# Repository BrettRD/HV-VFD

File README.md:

# HV-VFD
Staging point for design of a motor controller to suit electric vehicles.

This project is intended as a rework of https://github.com/vedderb/bldc-hardware/ to suit systems operating beyond the power ratings of the VESC 4.x.

## Major design goals:
* 400V tolerant system.
* 400A overcurrent survivability.
* FET desaturation detection.
* Maximise forward compatibility with existing development efforts.
* Traction power and logic level isolation
* Flexibility for alternate applications.

### FETs
This design will be based on the SEMiX402GB066HDs by Semikron, but will hopefully support everything in their SEMiX_2s pack.  
This sets the price point fairly high, but will require a rock solid gate driver design.  
I expect this project to branch for different IGBT sizes.  

### FET Drivers
The FET drivers need an estimated 6A to reach 400A IGBTs  
Currently designing around the 1EDI60H12AH by infineon

### Desaturation detector / phase shunt monitor
Depending on the required bandwidth for the phase shunts, a PWM based isolation amp like the IRF2277 might suffice.  
This design will also include a Vsat monitor on all fets, but probably just a fast comparator.  
Current best practice for IGBTs seems to be soft shutdown at some Vsat threshold, for MOSFETs Vsat only helps with estimating the total instantaneous heat power per junction.  

### Architecture
External logic lines will not be linked to traction power in any way.  
High voltage gate drivers are isolated by default, and are mostly available as single-gate drivers.  
Gate handling logic will be on the logic-side, so desat detect and shunt monitoring will all require isolation.  
Given the FET package and the current, the shunts will almost certainly be off-board which makes Hall effect sensors less of a design change.

## Considerations:
### Phase or Rail shunts:  
Phase shunt amplifiers need seperate power supplies and isolation gear, offset calibration is less trivial.  
Phase shunts measure both incoming and outgoing current. KCL should apply to the motor but when it doesn't, you want to know. This also allows automatic gain calibration.  
VESC5 looks like using phase shunts. Using isolation amps, this design could be left configurable. or I could include both.

### Crazy shit not yet dismissed:
* FPGA gate handling logic (iCE40 with yosys)  
  This allows us to do interesting things to the gate drive signals like configurable dead-time/overlap, spike quenching, fast ADCs and thermal modelling of FET junctions.
  Upgrading to the STM32F405VG (100pin pack) offers a 16b wide 80MHz DMA bus.
* ADCs on traction side of isolation barrier.  
  Saves on isolation amplifiers and noise.  
  The STM32F4 has a really nice ADC architecture with custom triggers, DMA, and 12b 6MS/s over 24 channels.

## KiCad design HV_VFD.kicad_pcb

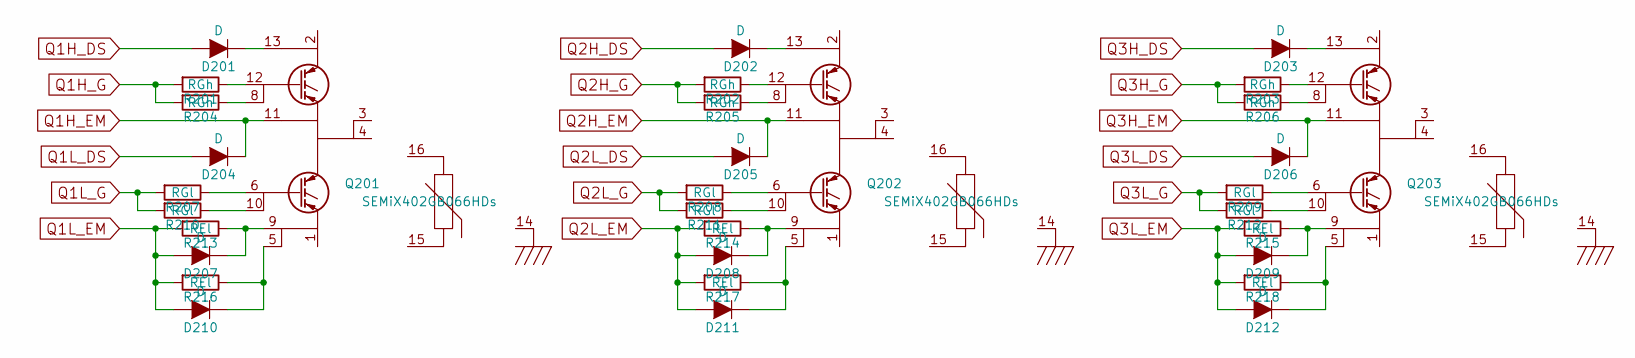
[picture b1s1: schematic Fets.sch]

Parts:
D201, D202, D203, D204, D205, D206: D; MELF_Standard
D207, D208, D209, D210, D211, D212: D; DO-214AB
Q201, Q202, Q203: SEMiX402GB066HDs; SEMiX_2s_7nc
R201, R202, R203, R204, R205, R206: RGh; R_1812
R207, R208, R209, R210, R211, R212: RGl; R_1812
R213, R214, R215, R216, R217, R218: REl; R_1812

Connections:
unnamed: D201.1 (K), Q201.13
unnamed: D202.1 (K), Q202.13
unnamed: D203.1 (K), Q203.13
unnamed: D207.1 (K), Q201.9, R213.1
unnamed: D208.1 (K), Q202.9, R214.1
unnamed: D209.1 (K), Q203.9, R215.1
unnamed: D210.1 (K), Q201.5, R216.1
unnamed: D211.1 (K), Q202.5, R217.1
unnamed: D212.1 (K), Q203.5, R218.1
unnamed: Q201.6, R207.1
unnamed: Q201.8, R204.1
unnamed: Q201.10, R210.1
unnamed: Q201.12, R201.1
unnamed: Q202.6, R208.1
unnamed: Q202.8, R205.1
unnamed: Q202.10, R211.1
unnamed: Q202.12, R202.1
unnamed: Q203.6, R209.1
unnamed: Q203.8, R206.1
unnamed: Q203.10, R212.1
unnamed: Q203.12, R203.1
Q1H_DS: D201.2 (A); also elsewhere on the board
Q1H_EM: D204.1 (K), Q201.11; also elsewhere on the board
Q1H_G: R201.2, R204.2; also elsewhere on the board
Q1L_DS: D204.2 (A); also elsewhere on the board
Q1L_G: R207.2, R210.2; also elsewhere on the board
Q2H_DS: D202.2 (A); also elsewhere on the board
Q2H_EM: D205.1 (K), Q202.11; also elsewhere on the board
Q2H_G: R202.2, R205.2; also elsewhere on the board
Q2L_DS: D205.2 (A); also elsewhere on the board
Q2L_G: R208.2, R211.2; also elsewhere on the board
Q3H_DS: D203.2 (A); also elsewhere on the board
Q3H_EM: D206.1 (K), Q203.11; also elsewhere on the board
Q3H_G: R203.2, R206.2; also elsewhere on the board
Q3L_DS: D206.2 (A); also elsewhere on the board
Q3L_G: R209.2, R212.2; also elsewhere on the board

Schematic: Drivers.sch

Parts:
C301, C302, C303, C304, C305, C306: C; C_1206
D301, D302, D303: D; MELF_Standard
R301, R302, R303, R310, R311, R312: R; R_0603
R304, R305, R306, R307, R308, R309: R; R_1812
U301, U302, U303, U304, U305, U306: 1EDI60H12AH; PG-DSO-8-59

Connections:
+15V: C301.1, C303.1, C305.1, D301.2 (A), D302.2 (A), D303.2 (A), R310.2, R311.2, R312.2, U304.6, U305.6, U306.6
GNDD: U301.3, U301.4, U302.4, U303.4, U304.4, U305.4, U306.4
unnamed: R304.2, U301.7
unnamed: R305.2, U302.7
unnamed: R306.2, U303.7
unnamed: R307.2, U304.7
unnamed: R308.2, U305.7
unnamed: R309.2, U306.7
unnamed: U301.2, U304.3
Q1H_BS: C302.1, D301.1 (K), R301.2, U301.6
Q1H_DS: R301.1; also elsewhere on the board
Q1H_EM: C302.2, U301.5; also elsewhere on the board
Q1H_G: R304.1, U301.8; also elsewhere on the board
Q1L_DS: R310.1; also elsewhere on the board
Q1L_G: R307.1, U304.8; also elsewhere on the board
Q2H_BS: C304.1, D302.1 (K), R302.2, U302.6
Q2H_DS: R302.1; also elsewhere on the board
Q2H_EM: C304.2, U302.5; also elsewhere on the board
Q2H_G: R305.1, U302.8; also elsewhere on the board
Q2L_DS: R311.1; also elsewhere on the board
Q2L_G: R308.1, U305.8; also elsewhere on the board
Q3H_BS: C306.1, D303.1 (K), R303.2, U303.6
Q3H_DS: R303.1; also elsewhere on the board
Q3H_EM: C306.2, U303.5; also elsewhere on the board
Q3H_G: R306.1, U303.8; also elsewhere on the board
Q3L_DS: R312.1; also elsewhere on the board
Q3L_G: R309.1, U306.8; also elsewhere on the board
VCC: U301.1, U302.1, U303.1, U304.1, U305.1, U306.1

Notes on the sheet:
Qxx_DS is the IGBT collector voltage clamped at the bootstrap rail voltage. -Used for Desaturation detection.
QxH_BS is the Bootstrap rail voltage of the high side drivers -This rail may need trickle charging.
The Eice Driver has a neat inverting pin behaviour Shown here wired to prohibit shoot-through Not the final gate logic.

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
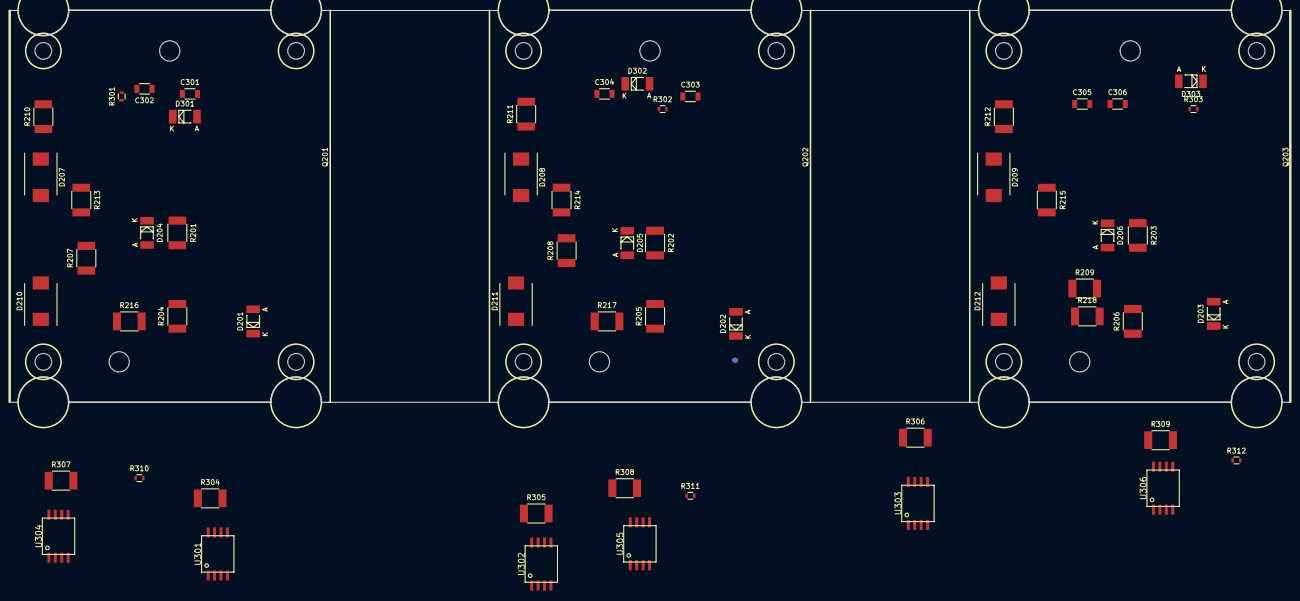
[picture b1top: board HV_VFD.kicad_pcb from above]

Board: 2 copper layers, 253.0 x 77.5 mm, 60 parts (0 on the bottom side), 51 nets.

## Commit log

2016-06-22 added footprint and PCB sizing experiments
2016-06-22 added basic bootstrap and desat diodes
2016-06-22 Added FET choice, updated target architecture.
2016-08-23 added gate drivers, increased FET spacing
2016-08-25 add notes.
